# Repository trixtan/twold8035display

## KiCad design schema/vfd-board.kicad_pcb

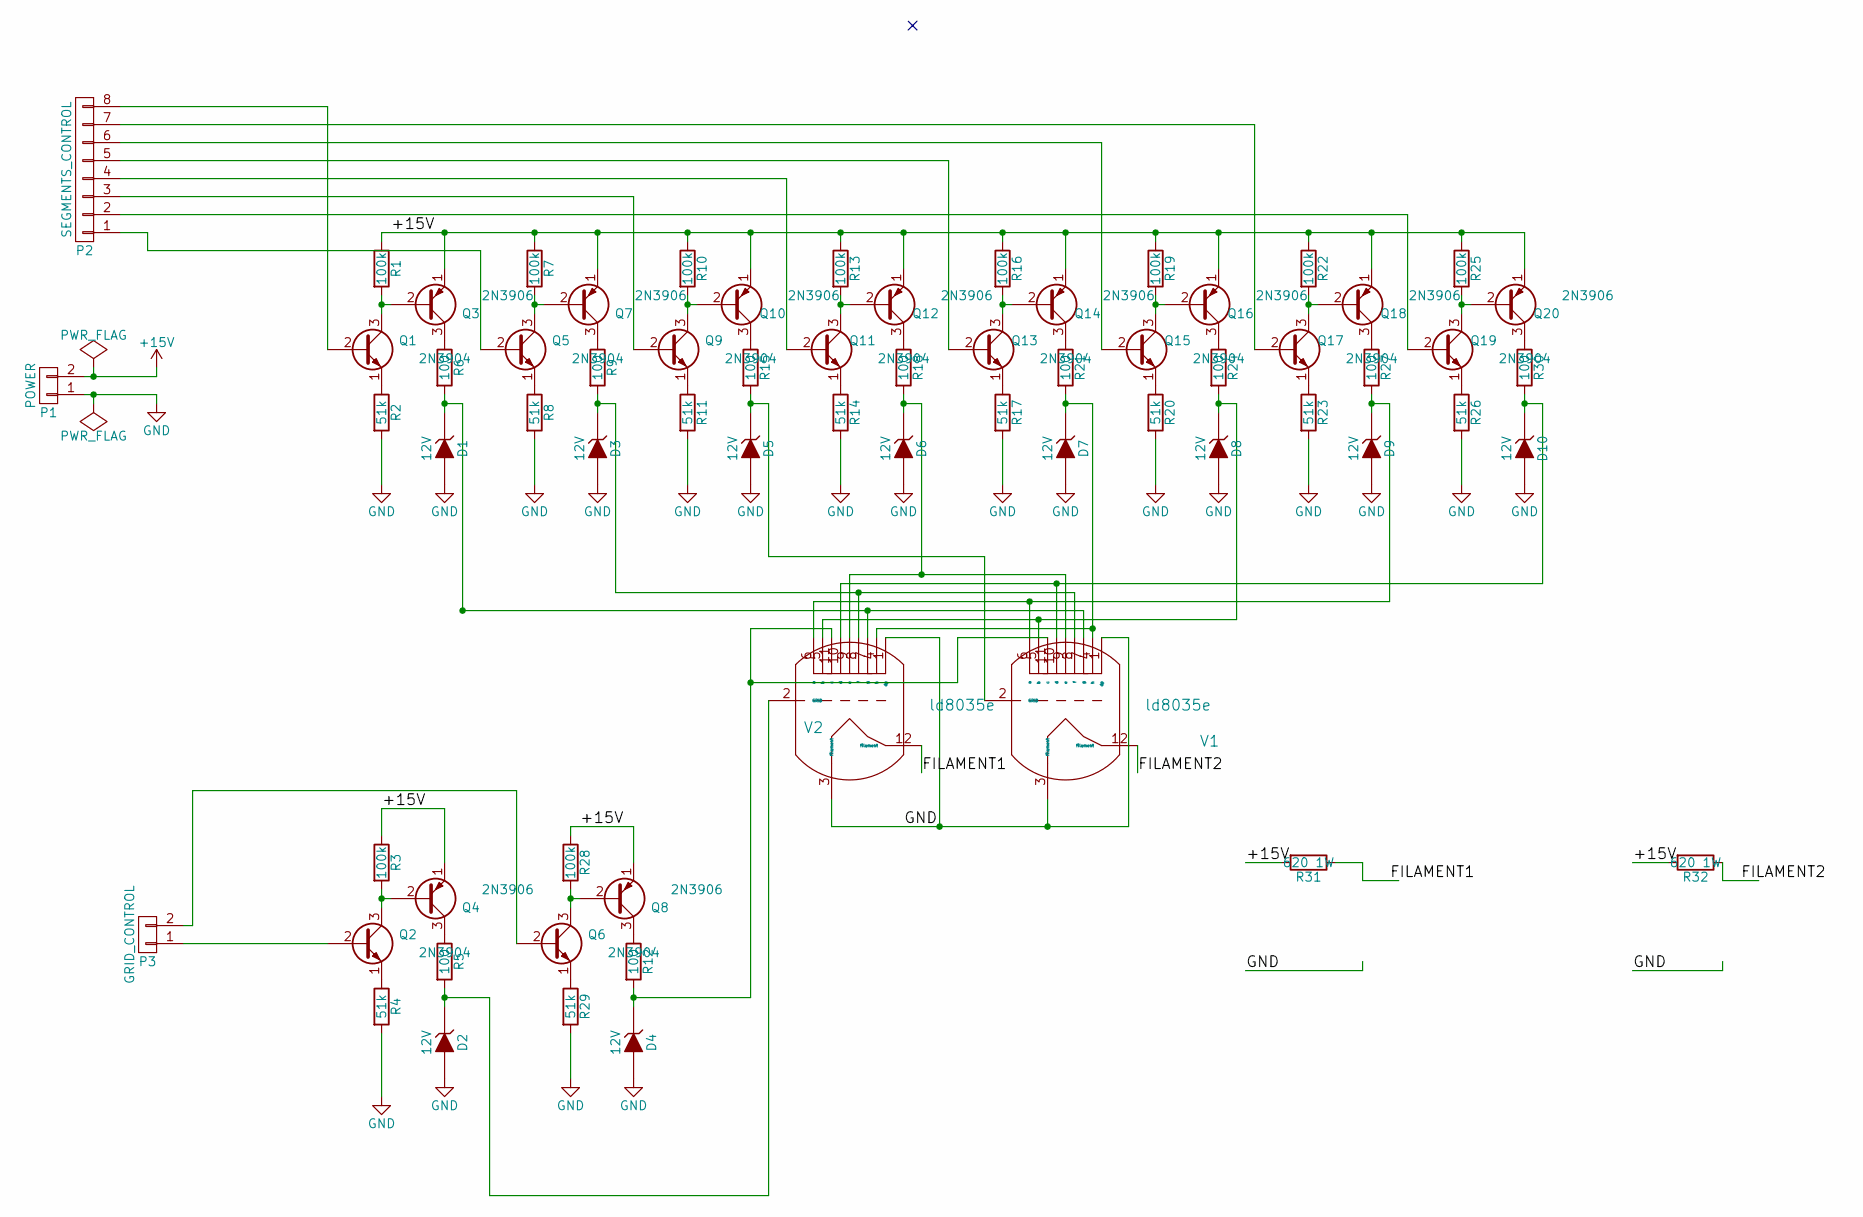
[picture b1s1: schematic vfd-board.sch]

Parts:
D1, D2, D3, D4, D5, D6, D7, D8, D9, D10: 12V; Diode_DO-41_SOD81_Horizontal_RM10
P1: POWER; Socket_Strip_Angled_1x02
P2: SEGMENTS_CONTROL; Socket_Strip_Angled_1x08
P3: GRID_CONTROL; Socket_Strip_Angled_1x02
Q1, Q2, Q5, Q6, Q9, Q11, Q13, Q15, Q17, Q19: 2N3904; TO-92_Molded_Narrow
Q3, Q4, Q7, Q8, Q10, Q12, Q14, Q16, Q18, Q20: 2N3906; TO-92_Molded_Narrow
R1, R3, R7, R10, R13, R16, R19, R22, R25, R28: 100k; Resistor_Horizontal_RM10mm
R2, R4, R8, R11, R14, R17, R20, R23, R26, R29: 51k; Resistor_Horizontal_RM10mm
R5, R6, R9, R12, R15, R18, R21, R24, R27, R30: 100; Resistor_Horizontal_RM10mm
R31, R32: 620 1W; Resistor_Horizontal_RM15mm
V1, V2: ld8035e; LD-8035-PERFBOARD

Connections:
+15V: P1.2, Q3.1 (E), Q4.1 (E), Q7.1 (E), Q8.1 (E), Q10.1 (E), Q12.1 (E), Q14.1 (E), Q16.1 (E), Q18.1 (E), Q20.1 (E), R1.1, R3.1, R7.1, R10.1, R13.1, R16.1, R19.1, R22.1, R25.1, R28.1, R31.2, R32.2
/FILAMENT1: R31.1, V2.12 (filament)
/FILAMENT2: R32.1, V1.12 (filament)
GND: D1.2 (A), D2.2 (A), D3.2 (A), D4.2 (A), D5.2 (A), D6.2 (A), D7.2 (A), D8.2 (A), D9.2 (A), D10.2 (A), P1.1, R2.2, R4.2, R8.2, R11.2, R14.2, R17.2, R20.2, R23.2, R26.2, R29.2, V1.1 (dp), V1.3 (filament), V2.1 (dp), V2.3 (filament)
unnamed: D1.1 (K), R6.2, V1.7 (g), V2.7 (g)
unnamed: D2.1 (K), R5.2, V2.2 (GRID)
unnamed: D3.1 (K), R9.2, V1.8 (f), V2.8 (f)
unnamed: D4.1 (K), R12.2, V1.11 (c), V2.11 (c)
unnamed: D5.1 (K), R15.2, V1.2 (GRID)
unnamed: D6.1 (K), R18.2, V1.9 (e), V2.9 (e)
unnamed: D7.1 (K), R21.2, V1.4 (h), V2.4 (h)
unnamed: D8.1 (K), R24.2, V1.5 (b), V2.5 (b)
unnamed: D9.1 (K), R27.2, V1.6 (a), V2.6 (a)
unnamed: D10.1 (K), R30.2, V1.10 (d), V2.10 (d)
unnamed: P2.1, Q5.2 (B)
unnamed: P2.2, Q19.2 (B)
unnamed: P2.3, Q9.2 (B)
unnamed: P2.4, Q11.2 (B)
unnamed: P2.5, Q13.2 (B)
unnamed: P2.6, Q15.2 (B)
unnamed: P2.7, Q17.2 (B)
unnamed: P2.8, Q1.2 (B)
unnamed: P3.1, Q2.2 (B)
unnamed: P3.2, Q6.2 (B)
unnamed: Q1.1 (E), R2.1
unnamed: Q1.3 (C), Q3.2 (B), R1.2
unnamed: Q2.1 (E), R4.1
unnamed: Q2.3 (C), Q4.2 (B), R3.2
unnamed: Q3.3 (C), R6.1
unnamed: Q4.3 (C), R5.1
unnamed: Q5.1 (E), R8.1
unnamed: Q5.3 (C), Q7.2 (B), R7.2
unnamed: Q6.1 (E), R29.1
unnamed: Q6.3 (C), Q8.2 (B), R28.2
unnamed: Q7.3 (C), R9.1
unnamed: Q8.3 (C), R12.1
unnamed: Q9.1 (E), R11.1
unnamed: Q9.3 (C), Q10.2 (B), R10.2
unnamed: Q10.3 (C), R15.1
unnamed: Q11.1 (E), R14.1
unnamed: Q11.3 (C), Q12.2 (B), R13.2
unnamed: Q12.3 (C), R18.1
unnamed: Q13.1 (E), R17.1
unnamed: Q13.3 (C), Q14.2 (B), R16.2
unnamed: Q14.3 (C), R21.1
unnamed: Q15.1 (E), R20.1
unnamed: Q15.3 (C), Q16.2 (B), R19.2
unnamed: Q16.3 (C), R24.1
unnamed: Q17.1 (E), R23.1
unnamed: Q17.3 (C), Q18.2 (B), R22.2
unnamed: Q18.3 (C), R27.1
unnamed: Q19.1 (E), R26.1
unnamed: Q19.3 (C), Q20.2 (B), R25.2
unnamed: Q20.3 (C), R30.1

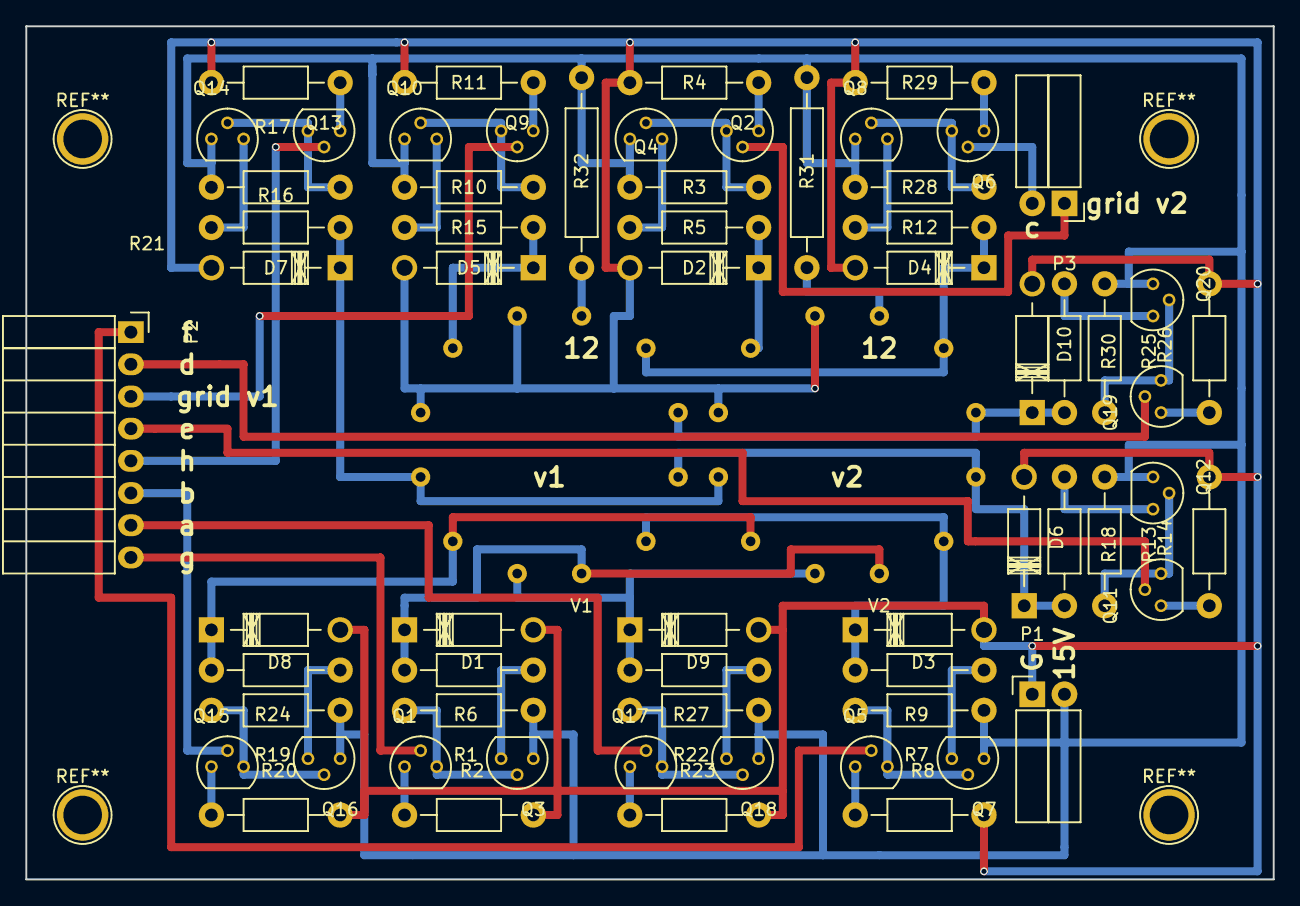
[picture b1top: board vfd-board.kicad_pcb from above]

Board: 2 copper layers, 98.4 x 67.3 mm, 67 parts (0 on the bottom side), 54 nets.

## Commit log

2016-12-18 Removed schema
2016-12-18 added P
